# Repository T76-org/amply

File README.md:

# Amply - a $10 Bluetooth amplifier you'll love

**Amply** is a compact, high-quality audio amplifier and Bluetooth receiver that can be built from roughly $10 worth of widely available parts.

Designed for desktop speakers, it delivers up to 2×10 W into 8 Ω loads while running from an ordinary USB-C power adapter. The entire design uses common, easy-to-source components, making it practical to build almost anywhere.

Despite its low cost, Amply offers surprisingly strong audio performance: THD below 0.015%, excellent linearity, and a flat response extending down to 20 Hz for deep bass, clean mids, and detailed highs.

- [Interactive BOM](./bom/ibom.html)
- [Interactive schematic](https://kicanvas.org/?repo=https%3A%2F%2Fgithub.com%2FT76-org%2Famply)
- [Production files](./production)
- [Reference 3D enclosure](./enclosure)

## Features

- 2-channel Bluetooth 5.0 audio receiver
    - Optional On/Off, muting, pause, next/previous track controls
- Class AB amplifier capable of delivering up to 2×10 W into 8 Ω
- THD (simulated) below 0.015% at 10W
- Largely-flat frequency response from 20 Hz to 20 kHz
- Powered by a standard USB-C power adapter (5-20 V, 1 A)

## Physical design

- Compact PCB design (100 mm × 100 mm)
- Fully open-source
- Easy to assemble; requires only basic soldering skills and a few common tools
- Uses widely available, low-cost components (total cost around $10)
- 3D-printed enclosure design included in the repository

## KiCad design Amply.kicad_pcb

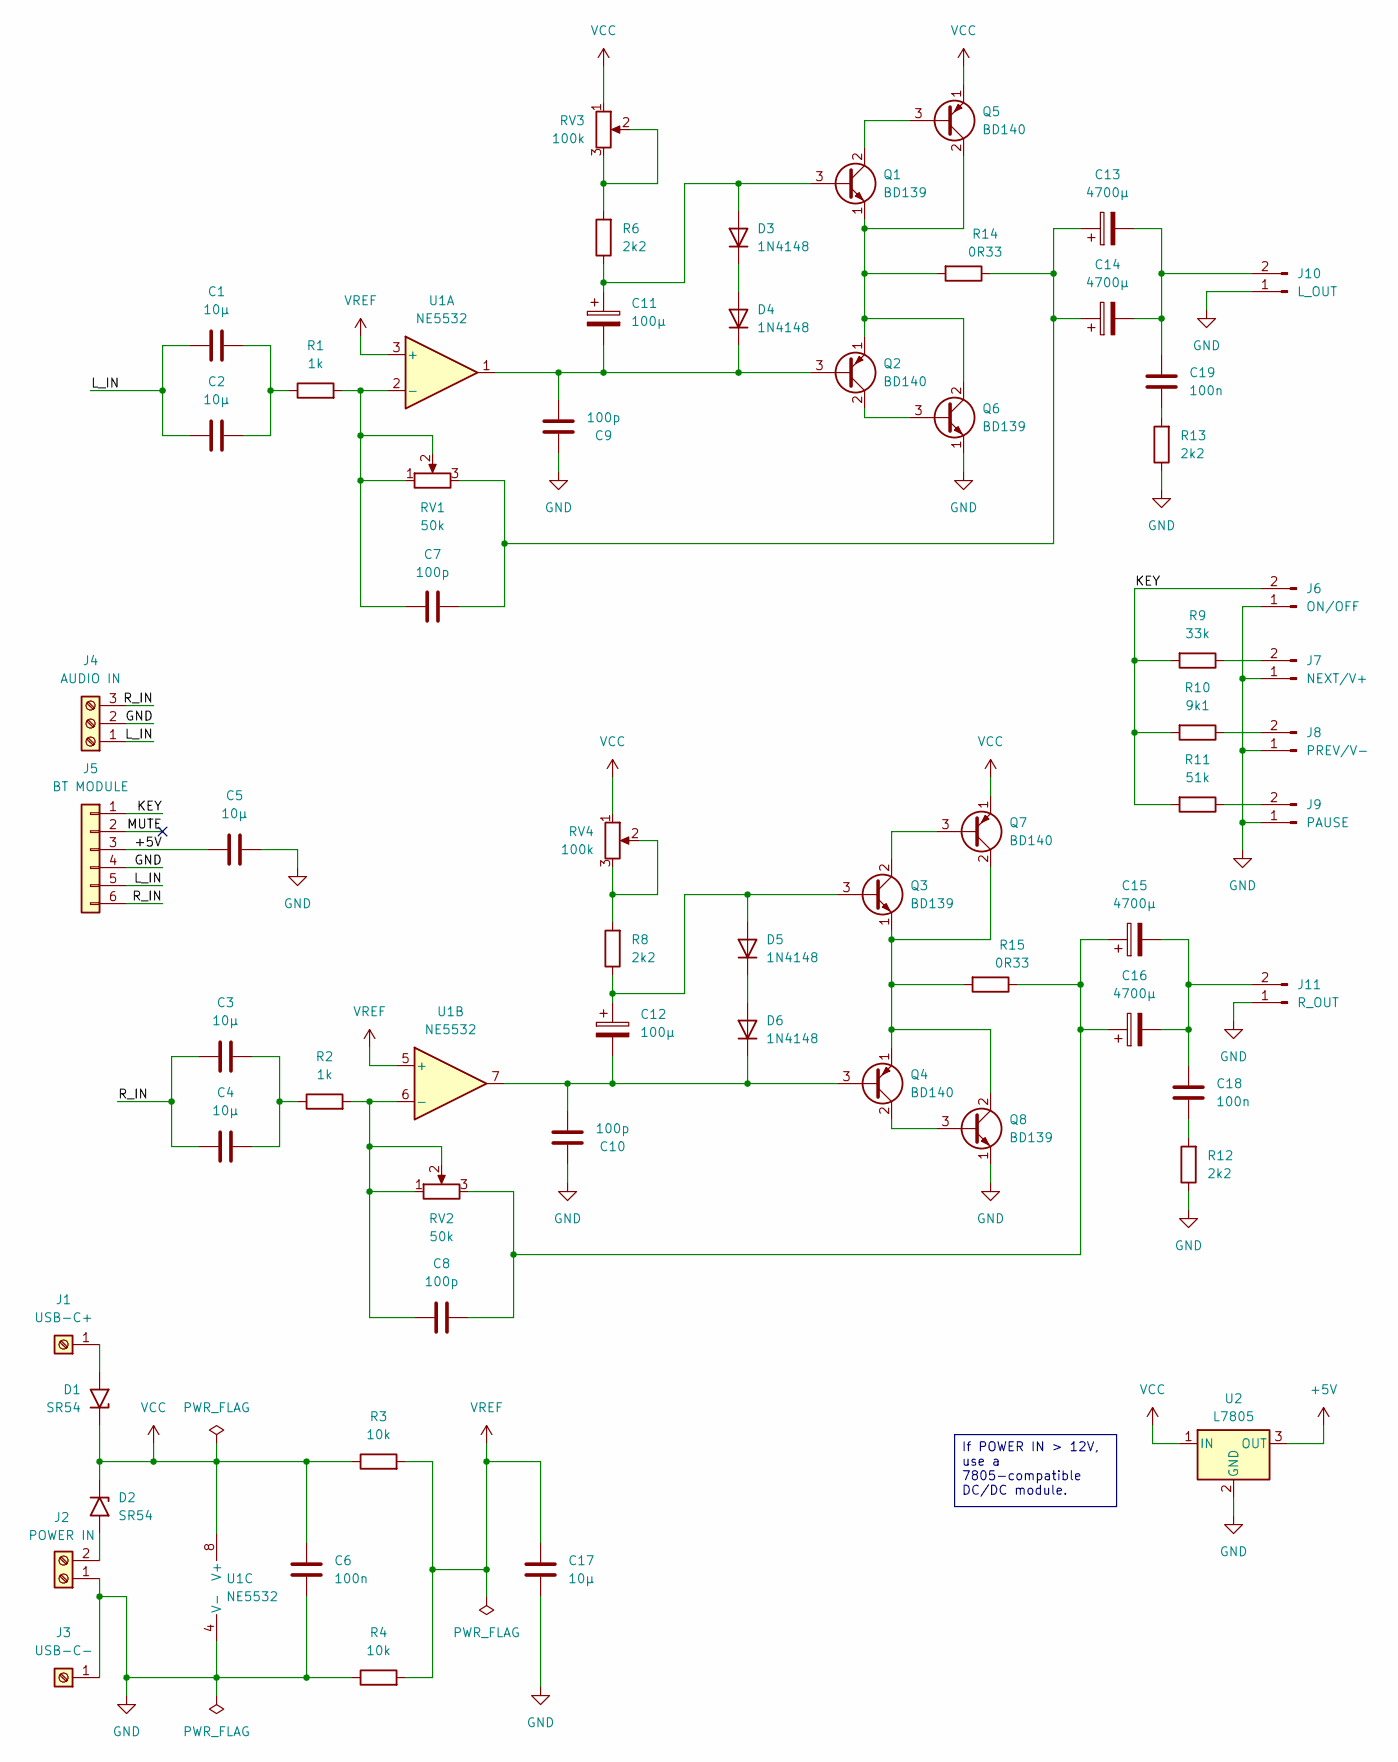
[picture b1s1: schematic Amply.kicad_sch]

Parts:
C1, C2, C3, C4, C5: 10µ; C_Disc_D6.0mm_W2.5mm_P5.00mm
C6, C18, C19: 100n; C_Disc_D5.0mm_W2.5mm_P2.50mm
C7, C8, C9, C10: 100p; C_Disc_D6.0mm_W2.5mm_P5.00mm
C11, C12: 100µ; CP_Radial_D8.0mm_P3.80mm
C13, C14, C15, C16: 4700µ; CP_Radial_D17.0mm_P7.50mm
C17: 10µ; C_Disc_D5.0mm_W2.5mm_P2.50mm
D1, D2: SR54; D_DO-201AE_P15.24mm_Horizontal
D3, D4, D5, D6: 1N4148; D_DO-35_SOD27_P7.62mm_Horizontal
J1: USB-C+; SolderWirePad_1x01_SMD_2x4mm
J2: POWER IN; PinHeader_1x02_P2.54mm_Vertical
J3: USB-C-; SolderWirePad_1x01_SMD_2x4mm
J4: AUDIO IN; PinHeader_1x03_P2.54mm_Vertical
J5: BT MODULE; PinHeader_1x06_P2.54mm_Vertical
J6: ON/OFF; PinHeader_1x02_P2.54mm_Vertical
J7: NEXT/V+; PinHeader_1x02_P2.54mm_Vertical
J8: PREV/V-; PinHeader_1x02_P2.54mm_Vertical
J9: PAUSE; PinHeader_1x02_P2.54mm_Vertical
J10: L_OUT; PinHeader_1x02_P2.54mm_Vertical
J11: R_OUT; PinHeader_1x02_P2.54mm_Vertical
Q1, Q3, Q6, Q8: BD139; TO-126-3_Vertical
Q2, Q4, Q5, Q7: BD140; TO-126-3_Vertical
R1, R2: 1k; R_Axial_DIN0207_L6.3mm_D2.5mm_P7.62mm_Horizontal
R3, R4: 10k; R_Axial_DIN0207_L6.3mm_D2.5mm_P7.62mm_Horizontal
R6, R8, R12, R13: 2k2; R_Axial_DIN0207_L6.3mm_D2.5mm_P7.62mm_Horizontal
R9: 33k; R_Axial_DIN0207_L6.3mm_D2.5mm_P7.62mm_Horizontal
R10: 9k1; R_Axial_DIN0207_L6.3mm_D2.5mm_P7.62mm_Horizontal
R11: 51k; R_Axial_DIN0207_L6.3mm_D2.5mm_P7.62mm_Horizontal
R14, R15: 0R33; R_Axial_DIN0414_L11.9mm_D4.5mm_P7.62mm_Vertical
RV1, RV2: 50k; Potentiometer_Runtron_RM-065_Vertical
RV3, RV4: 100k; Potentiometer_Runtron_RM-065_Vertical
U1: NE5532; DIP-8_W7.62mm_LongPads
U2: L7805; TO-220-3_Vertical

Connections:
+5V: C5.1, J5.3, U2.3 (OUT)
/KEY: J5.1, J6.2, R9.2, R10.2, R11.2
/L_IN: C1.1, C2.1, J4.1, J5.5
/MUTE: J5.2
/R_IN: C3.1, C4.1, J4.3, J5.6
GND: C5.2, C6.2, C9.1, C10.1, C17.2, J2.1, J3.1, J4.2, J5.4, J6.1, J7.1, J8.1, J9.1, J10.1, J11.1, Q6.1 (E), Q8.1 (E), R4.1, R12.1, R13.1, U1.4 (V-), U2.2 (GND)
unnamed: C1.2, C2.2, R1.1
unnamed: C3.2, C4.2, R2.1
unnamed: C7.2, C13.1, C14.1, R14.1, RV1.3
unnamed: C8.2, C15.1, C16.1, R15.1, RV2.3
unnamed: C18.2, R12.2
unnamed: C19.2, R13.2
unnamed: D1.2 (A2), J1.1
unnamed: D2.2 (A2), J2.2
unnamed: C11.1, D3.2 (A), Q1.3 (B), R6.1
unnamed: D3.1 (K), D4.2 (A)
unnamed: C9.2, C11.2, D4.1 (K), Q2.3 (B), U1.1
unnamed: C12.1, D5.2 (A), Q3.3 (B), R8.1
unnamed: D5.1 (K), D6.2 (A)
unnamed: C10.2, C12.2, D6.1 (K), Q4.3 (B), U1.7
unnamed: J7.2, R9.1
unnamed: J8.2, R10.1
unnamed: J9.2, R11.1
unnamed: C13.2, C14.2, C19.1, J10.2
unnamed: C15.2, C16.2, C18.1, J11.2
unnamed: Q1.2 (C), Q5.3 (B)
unnamed: Q1.1 (E), Q2.1 (E), Q5.2 (C), Q6.2 (C), R14.2
unnamed: Q2.2 (C), Q6.3 (B)
unnamed: Q3.2 (C), Q7.3 (B)
unnamed: Q3.1 (E), Q4.1 (E), Q7.2 (C), Q8.2 (C), R15.2
unnamed: Q4.2 (C), Q8.3 (B)
unnamed: R6.2, RV3.2, RV3.3
unnamed: R8.2, RV4.2, RV4.3
unnamed: C7.1, R1.2, RV1.1, RV1.2, U1.2 (-)
unnamed: C8.1, R2.2, RV2.1, RV2.2, U1.6 (-)
VCC: C6.1, D1.1 (A1), D2.1 (A1), Q5.1 (E), Q7.1 (E), R3.1, RV3.1, RV4.1, U1.8 (V+), U2.1 (IN)
VREF: C17.1, R3.2, R4.2, U1.3 (+), U1.5 (+)

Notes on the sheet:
If POWER IN > 12V, use a 7805-compatible DC/DC module.

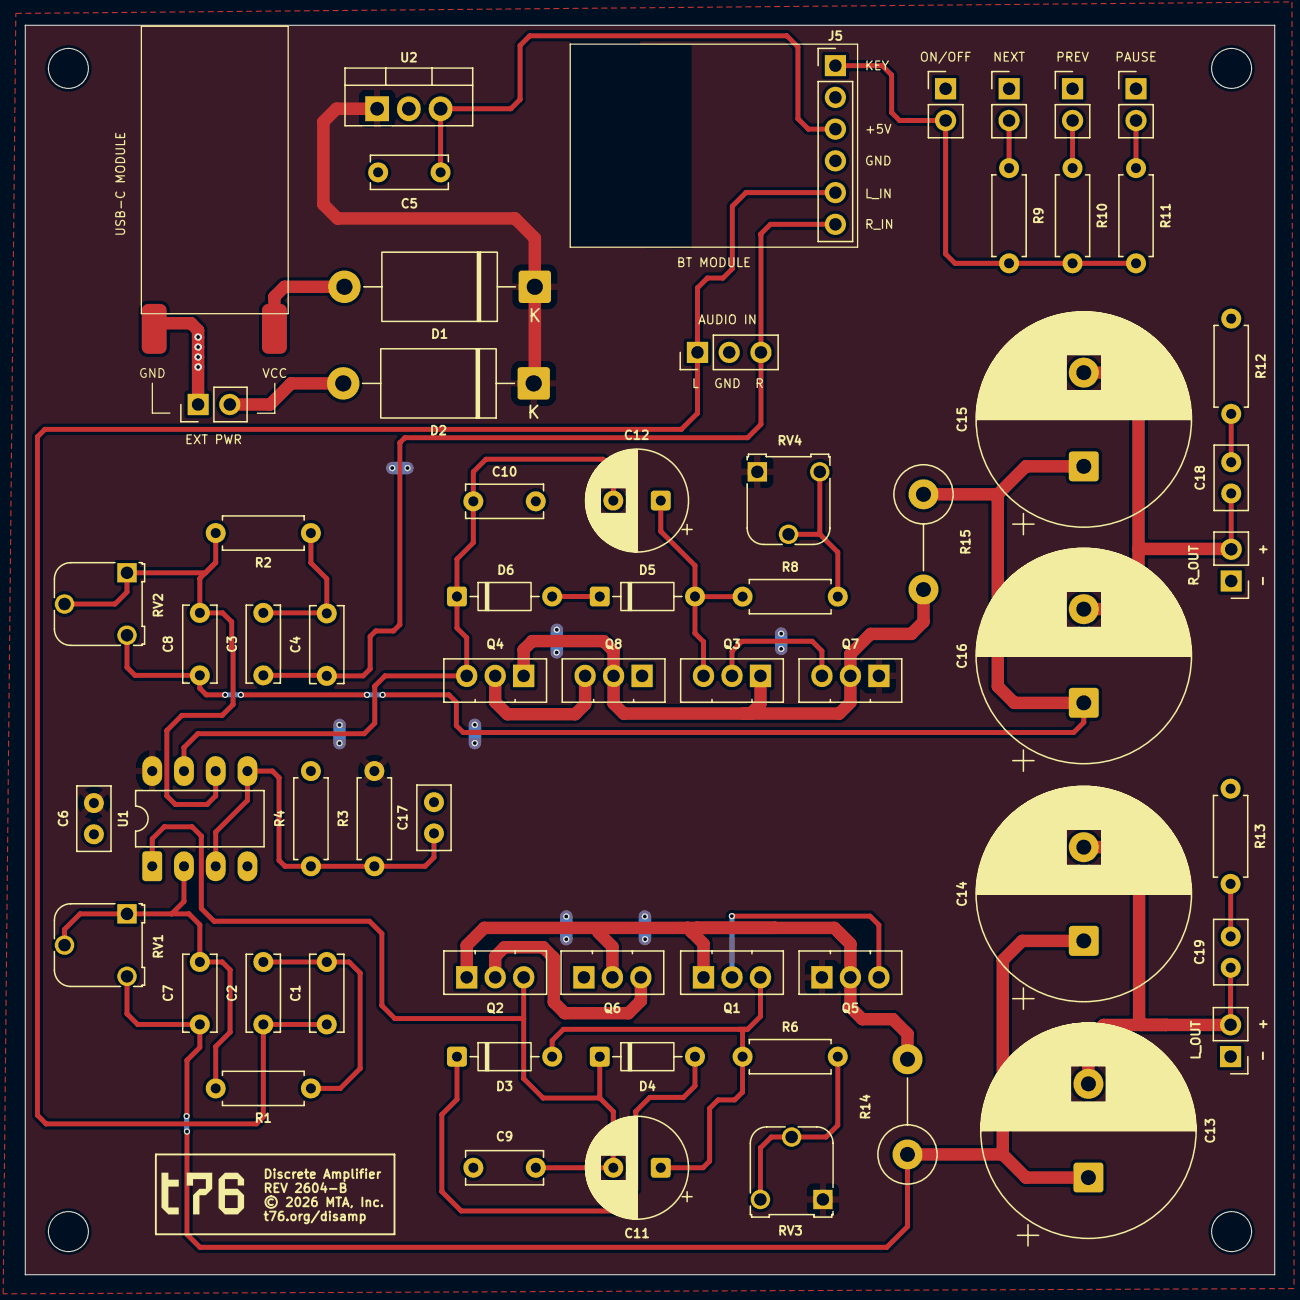
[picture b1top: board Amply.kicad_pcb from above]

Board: 2 copper layers, 100.0 x 100.0 mm, 63 parts (0 on the bottom side), 36 nets.

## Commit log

2026-05-06 - Enclosure - Gerbers - Update README
2026-05-06 Update README.md with production files and reference enclosure; remove obsolete fabrication toolkit and production files

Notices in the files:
Amply.kicad_pcb:
© MTA, Inc.
Released under GPLv3
© 2026 MTA, Inc.
